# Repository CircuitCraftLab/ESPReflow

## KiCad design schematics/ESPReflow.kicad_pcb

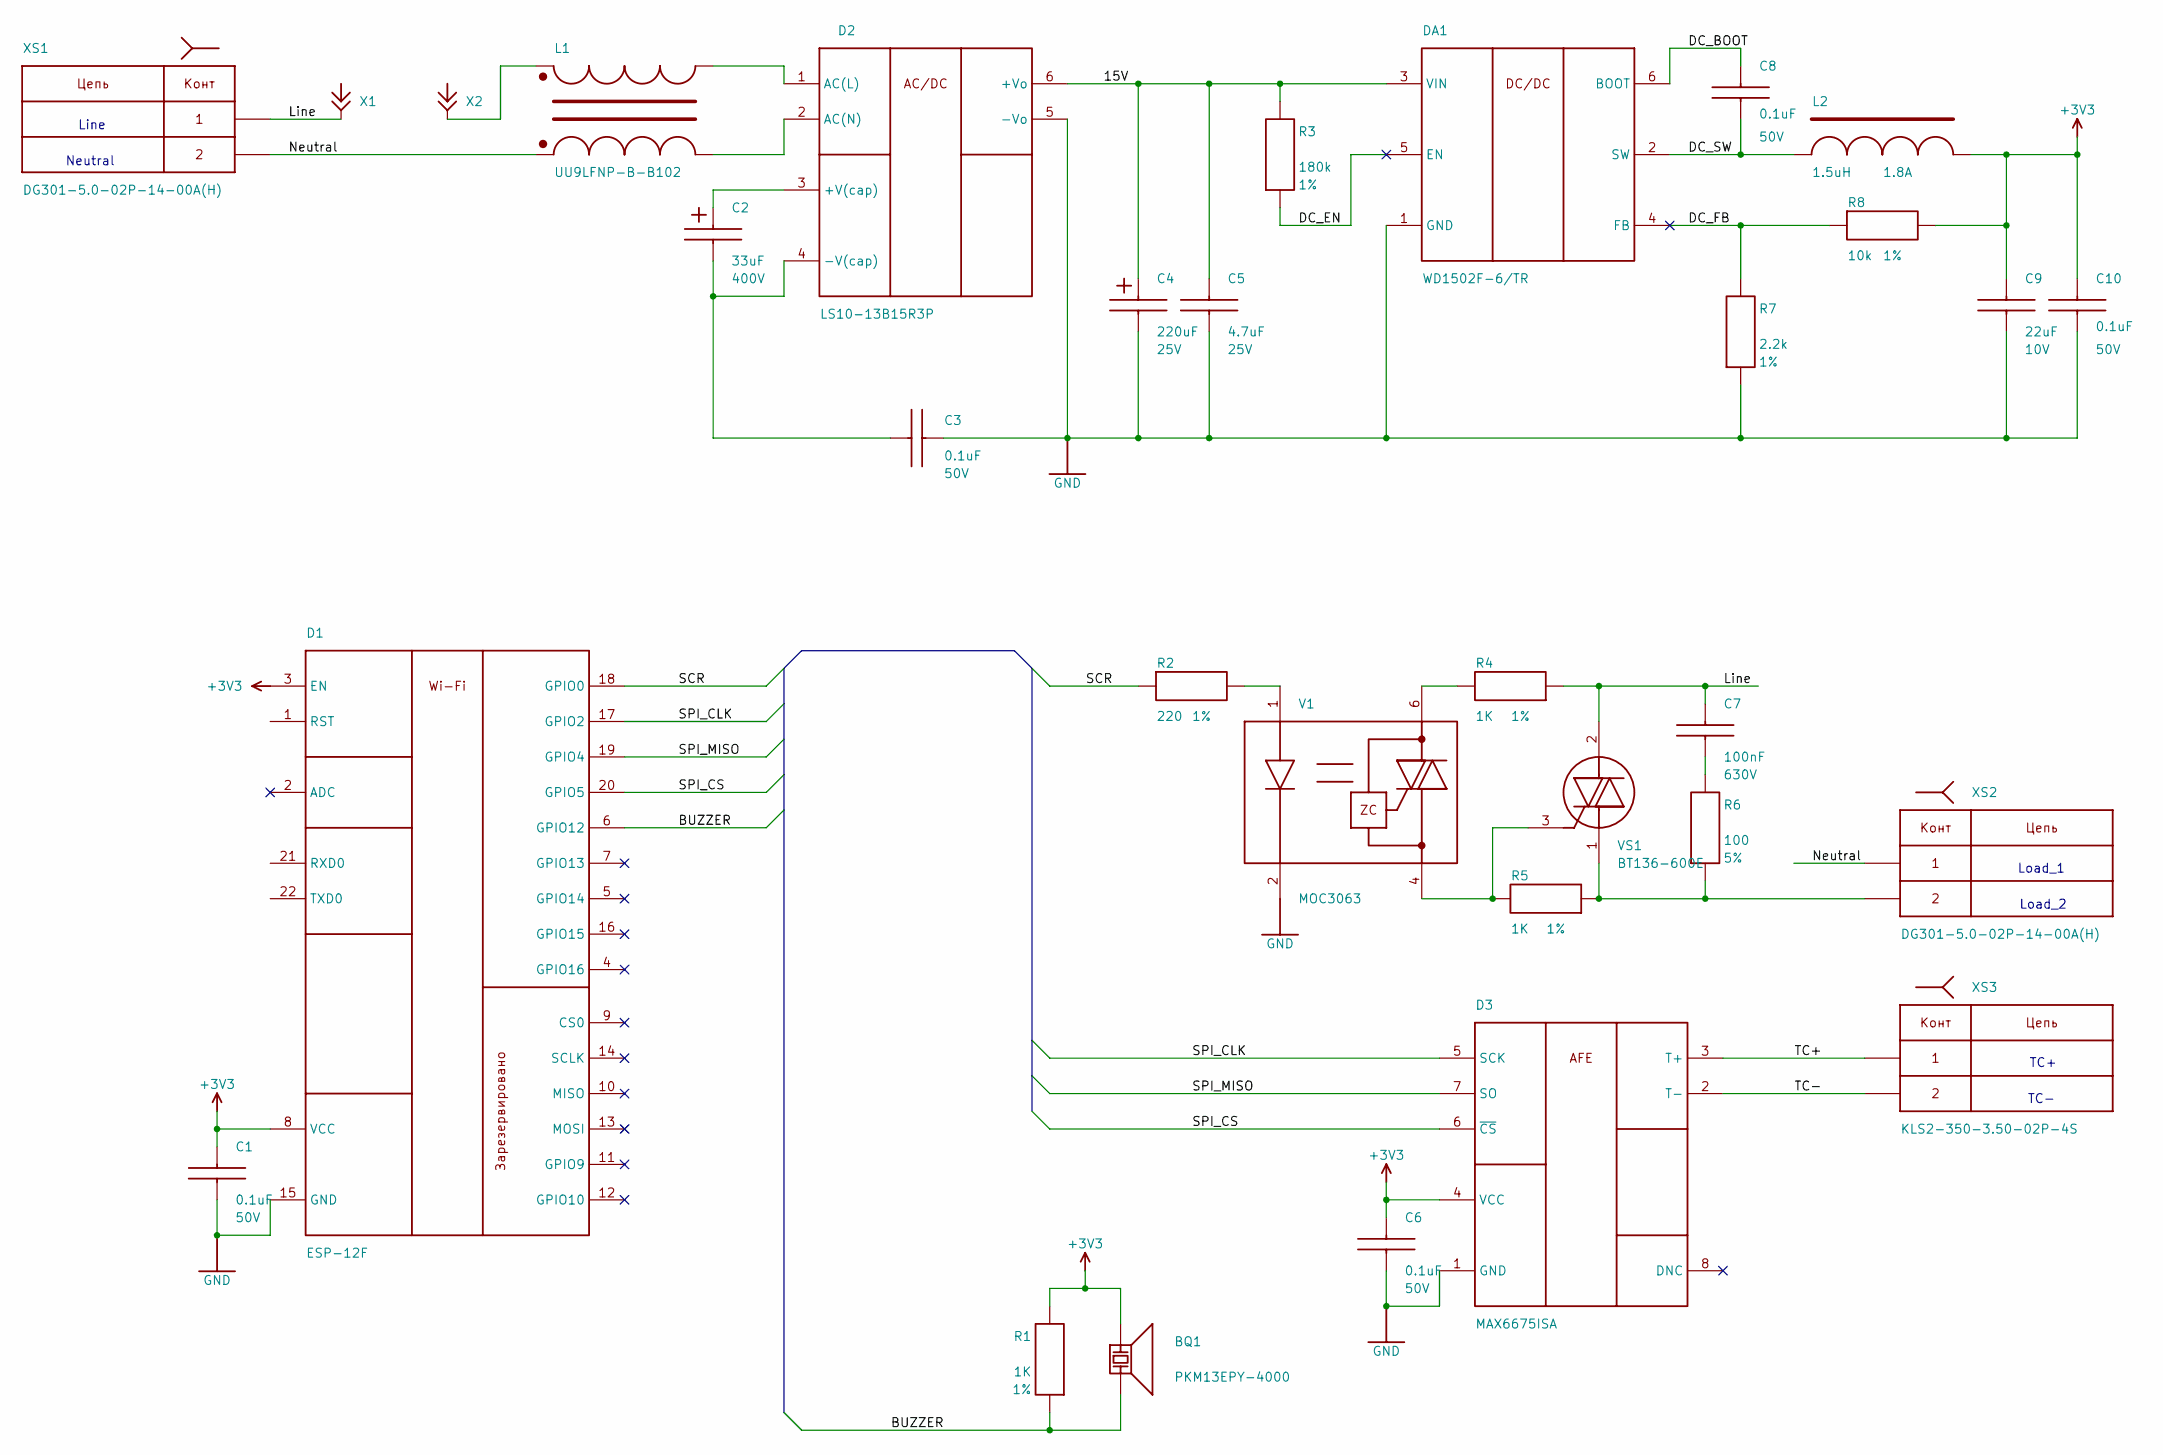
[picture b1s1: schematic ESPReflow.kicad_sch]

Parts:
BQ1: PKM13EPY-4000; R_D12p6_H6p9_S5_d0p5; PART NUMBER PKM13EPY-4000
C1, C3, C6, C8, C10: 0.1uF; CAPC1608X09N; VOLTAGE 50V; TOLERANCE 10%; PART NUMBER 0603-0.1uF-50V-10%-X7R
C2: 33uF; CAPPRD800W80D1650H2200; VOLTAGE 400V; PART NUMBER CG330MOD20BP
C4: 220uF; CAPPRD400W50D850H1350; VOLTAGE 25V; PART NUMBER 03EC0360
C5: 4.7uF; CAPC3216X19N; VOLTAGE 25V; TOLERANCE 10%; PART NUMBER 1206-4.7uF-25V-10%-X7R
C7: 100nF; CAPRR1600W70L1750T600H1200; VOLTAGE 630V; TOLERANCE 5%; PART NUMBER MEF104J2J6AS6040A1
C9: 22uF; CAPC3216X19N; VOLTAGE 10V; TOLERANCE 10%; PART NUMBER 1206-22uF-10V-10%-X7R
D1: ESP-12F; PART NUMBER ESP-12F
D2: LS10-13B15R3P; LS10-13BxxR3P_LUT; PART NUMBER LS10-13B15R3P
D3: MAX6675ISA; SOIC8P127_490X600X175L83X42N; PART NUMBER MAX6675ISA
DA1: WD1502F-6/TR; SOT23-6P95_280X90L45X42N; PART NUMBER WD1502F-6/TR
L1: UU9LFNP-B-B102; UU9LF; PART NUMBER UU9LFNP-B-B102
L2: 1.5uH; INDP400L400WX180_N; TOLERANCE 30%; PART NUMBER SWPA4018S1R5NT
R1, R4, R5: 1K; RESC1608X55N; TOLERANCE 1%; PART NUMBER 0603-1K-1%-1/10 W-100ppm
R2: 220; RESC1608X55N; TOLERANCE 1%; PART NUMBER 0603-220-1%-1/10 W-100ppm
R3: 180k; RESC1608X55N; TOLERANCE 1%; PART NUMBER 0603-180K-1%-1/10W-100ppm
R6: 100; MF-05W_RESAD1400W60L1000D500; TOLERANCE 5%; PART NUMBER MF0W2JJ0101A10
R7: 2.2k; RESC1608X55N; TOLERANCE 1%; PART NUMBER 0603-2.2K-1%-1/10W-100ppm
R8: 10k; RESC1608X55N; TOLERANCE 1%; PART NUMBER 0603-10k-1%-1/10 W-100ppm
V1: MOC3063; DIP-6_DIP762W50P254L735H400Q6; PART NUMBER MOC3063
VS1: BT136-600Е; TO-220C_TO254_440P1040X460X2000-3; PART NUMBER BT136-600Е
X1, X2: Fuse_clip_5x20; Fuse clip 5x20; PART NUMBER Fuse_clip_5x20
XS1, XS2: DG301-5.0-02P-14-00A(H); DG301-5.0-02P; PART NUMBER DG301-5.0-02P-14-00A(H)
XS3: KLS2-350-3.50-02P-4S; PART NUMBER KLS2-350-3.50-02P-4S

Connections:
15V: C4.2, C5.1, D2.6 (+Vo), DA1.3 (VIN), R3.2
+3V3: BQ1.1, C1.1, C6.1, C9.1, C10.1, D1.3 (EN), D1.8 (VCC), D3.4 (VCC), L2.2, R1.2, R8.2
BUZZER: BQ1.2, D1.6 (GPIO12), R1.1
DC_BOOT: C8.1, DA1.6 (BOOT)
DC_EN: DA1.5 (EN), R3.1
DC_FB: DA1.4 (FB), R7.2, R8.1
DC_SW: C8.2, DA1.2 (SW), L2.1
GND: C1.2, C3.2, C4.1, C5.2, C6.2, C9.2, C10.2, D1.15 (GND), D2.5 (-Vo), D3.1 (GND), DA1.1 (GND), R7.1, V1.2 (-)
Line: C7.1, R4.1, VS1.2 (T2), X1.1, XS1.1
NetC2_1: C2.1, C3.1, D2.4 (-V(cap))
NetC2_2: C2.2, D2.3 (+V(cap))
NetC7_2: C7.2, R6.2
NetD2_1: D2.1 (AC(L)), L1.2
NetD2_2: D2.2 (AC(N)), L1.3
NetL1_1: L1.1, X2.1
NetR2_2: R2.2, V1.1 (+)
NetR4_2: R4.2, V1.6
NetR5_1: R5.1, R6.1, VS1.1 (T1), XS2.2
NetR5_2: R5.2, V1.4, VS1.3 (G)
Neutral: L1.4, XS1.2, XS2.1
SCR: D1.18 (GPIO0), R2.1
SPI_CLK: D1.17 (GPIO2), D3.5 (SCK)
SPI_CS: D1.20 (GPIO5), D3.6 (~CS)
SPI_MISO: D1.19 (GPIO4), D3.7 (SO)
TC+: D3.3 (T+), XS3.1
TC-: D3.2 (T-), XS3.2

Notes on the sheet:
Load_1
Neutral
Load_2
Line
TC-
TC+

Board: 2 copper layers, 32 parts (17 on the bottom side), 26 nets, no tracks yet.

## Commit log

2024-01-05 Fixed errors, change pinout
2024-01-05 Some code refactoring, commented code which realize work PCA9536
2024-01-09 Add new schematic project.
2024-01-12 Changed schematic
2024-01-22 Change schematic
2024-02-06 Add PCB
2024-03-17 Add kicad project
